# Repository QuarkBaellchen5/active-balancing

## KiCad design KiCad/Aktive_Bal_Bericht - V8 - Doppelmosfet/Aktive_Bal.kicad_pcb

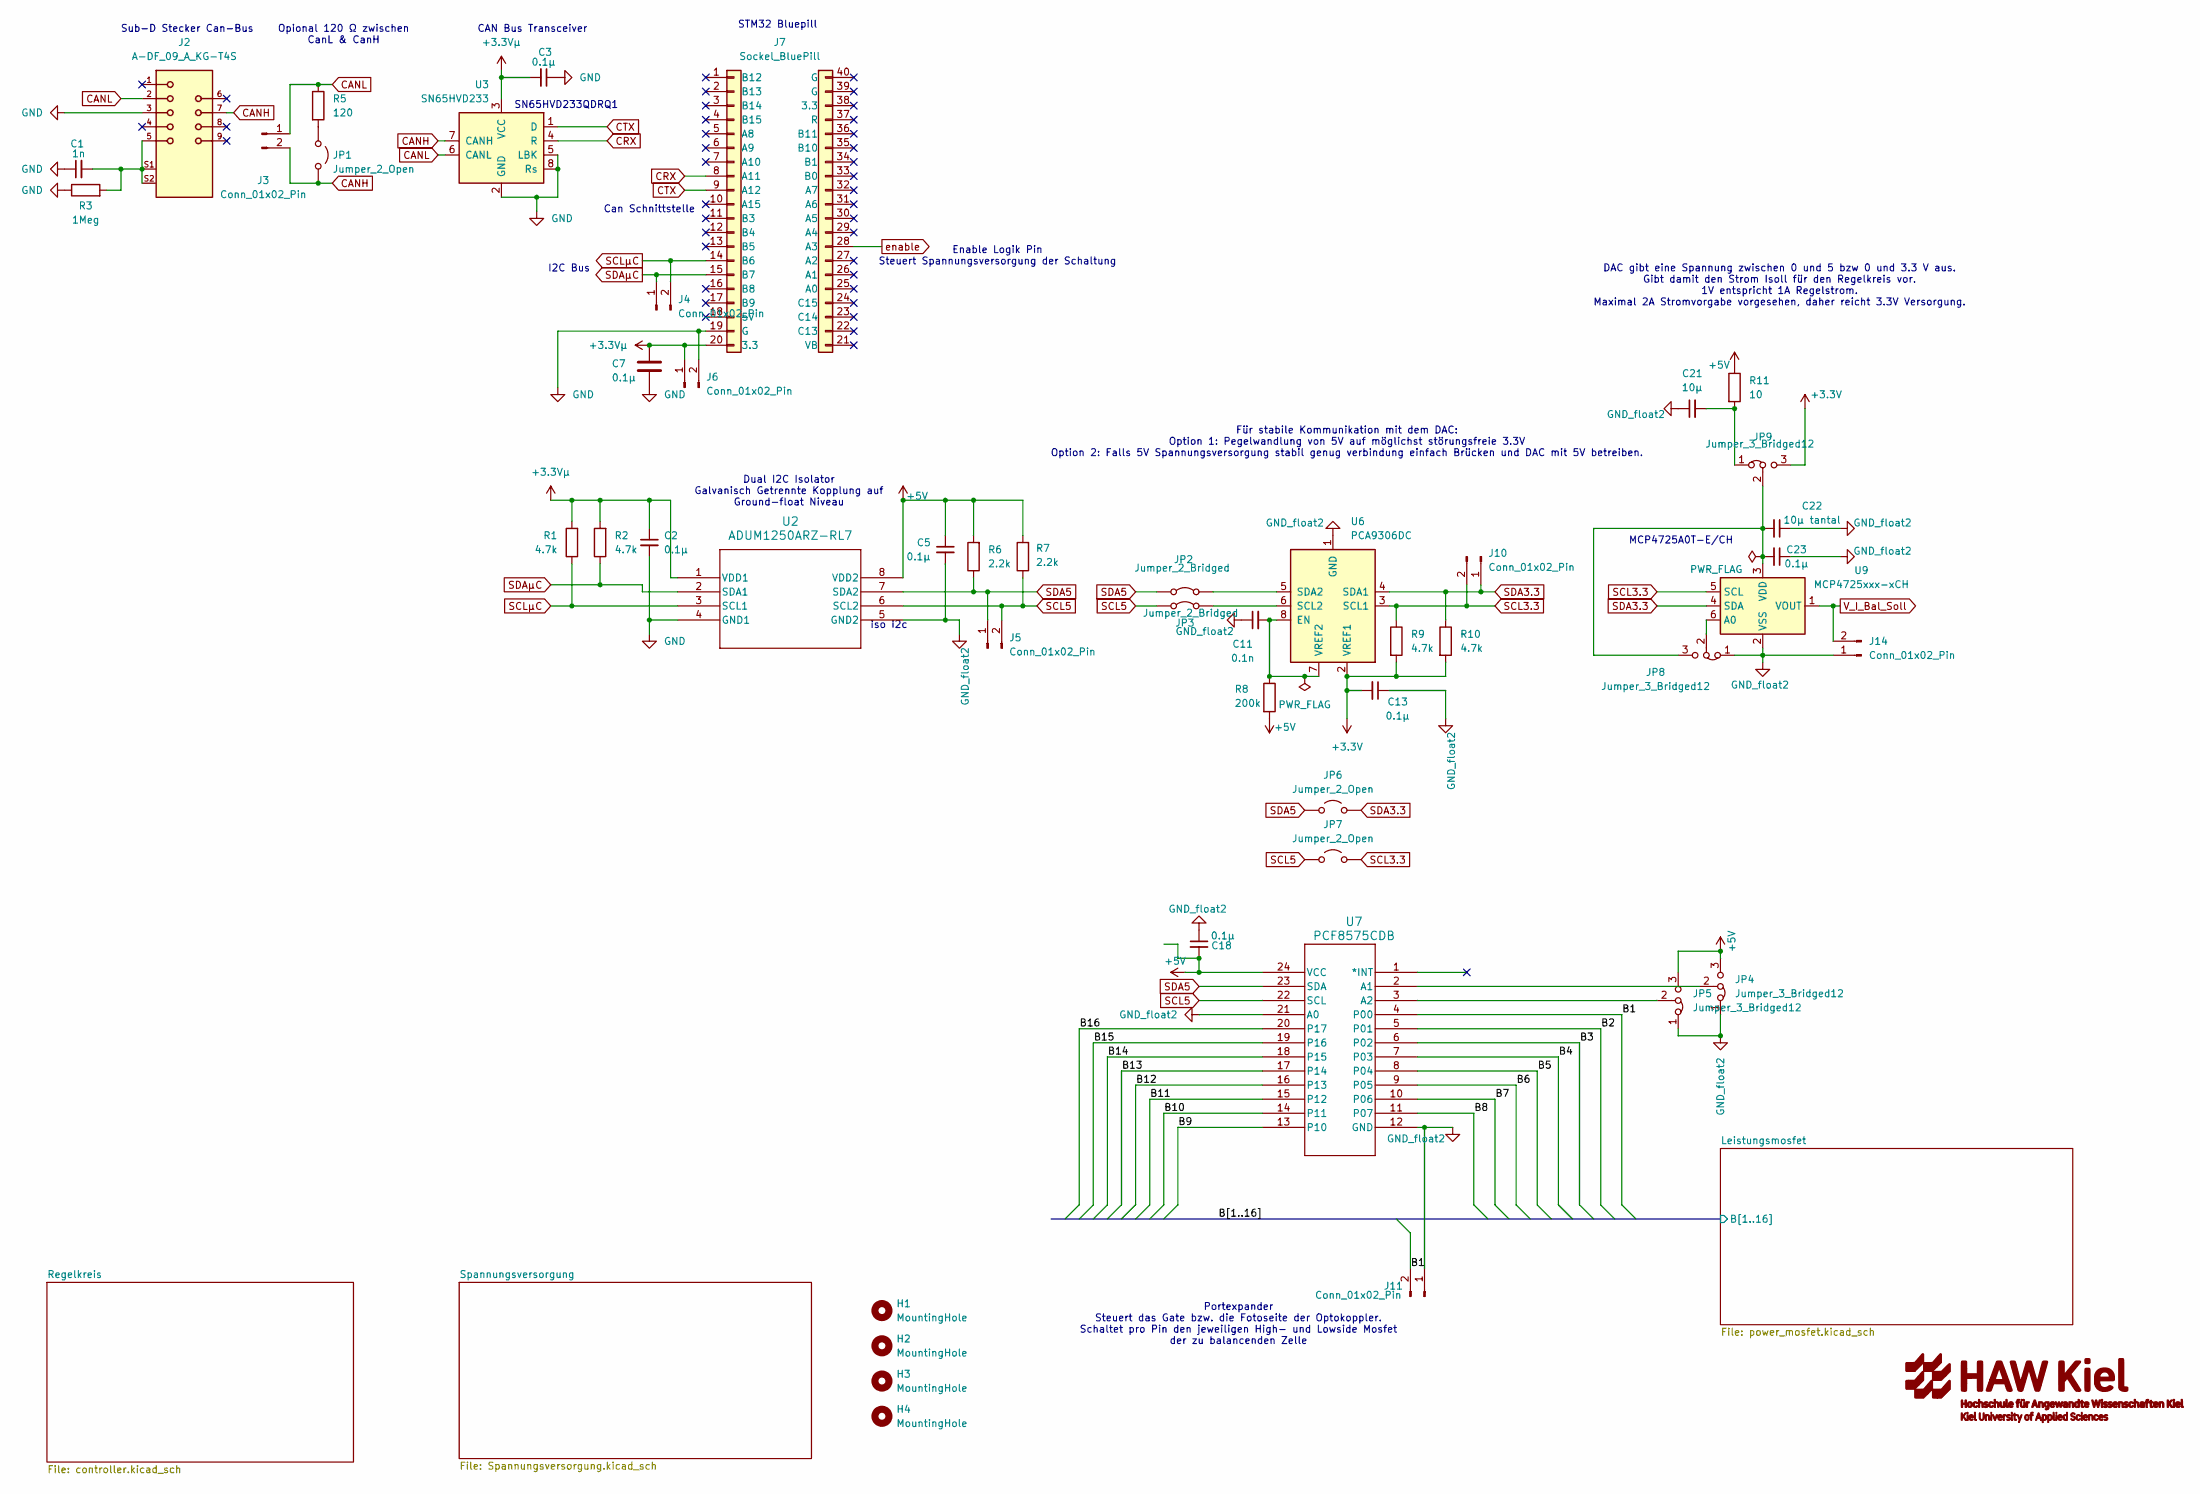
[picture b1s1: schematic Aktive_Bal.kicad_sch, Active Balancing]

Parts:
C1: 1n; C_0805_2012Metric
C2, C3, C5, C7, C13, C18, C23: 0.1µ; C_0805_2012Metric
C11: 0.1n; C_0805_2012Metric
C21: 10µ; C_0805_2012Metric
C22: 10µ tantal; C_0805_2012Metric
H1, H2, H3, H4: MountingHole; MountingHole_3.2mm_M3
J2: A-DF_09_A_KG-T4S; ASSMANN_A-DF_09_A_KG-T4S; PARTREV 05
J3, J4, J5, J6, J10, J11, J14: Conn_01x02_Pin; PinHeader_1x02_P2.54mm_Vertical
J7: Sockel_BluePill; SockelBluepill Dupont leisten
JP1, JP6, JP7: Jumper_2_Open; PinHeader_1x02_P2.54mm_Vertical
JP2, JP3: Jumper_2_Bridged; PinHeader_1x02_P2.54mm_Vertical
JP4, JP5, JP8, JP9: Jumper_3_Bridged12; PinHeader_1x03_P2.54mm_Vertical
R1, R2, R9, R10: 4.7k; R_0805_2012Metric
R3: 1Meg; R_0805_2012Metric
R5: 120; R_0805_2012Metric
R6, R7: 2.2k; R_0805_2012Metric
R8: 200k; R_0805_2012Metric
R11: 10; R_0805_2012Metric
U2: ADUM1250ARZ-RL7; ADUM1250ARZ-RL7_R_8_ADI-M
U3: SN65HVD233; SOIC-8_3.9x4.9mm_P1.27mm
U6: PCA9306DC; VSSOP-8_2.3x2mm_P0.5mm
U7: PCF8575CDB; PCF8575CDB_SSOP-24_5.3x8.2mm_P0.65mm
U9: MCP4725xxx-xCH; SOT-23-6

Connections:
+3.3V: C13.2, JP9.3 (B), R9.2, R10.2, U6.2 (VREF1); also elsewhere on the board
+3.3Vµ: C2.1, C3.2, C7.1, J6.1, J7.20 (3.3), R1.2, R2.2, U2.1 (VDD1), U3.3 (VCC)
+5V: C5.1, C18.2, JP4.3 (B), JP5.3 (B), R6.2, R7.2, R8.2, R11.1, U2.8 (VDD2), U7.24 (VCC); also elsewhere on the board
/B1: J11.2, U7.4 (P00); also elsewhere on the board
/B2: U7.5 (P01); also elsewhere on the board
/B3: U7.6 (P02); also elsewhere on the board
/B4: U7.7 (P03); also elsewhere on the board
/B5: U7.8 (P04); also elsewhere on the board
/B6: U7.9 (P05); also elsewhere on the board
/B7: U7.10 (P06); also elsewhere on the board
/B8: U7.11 (P07); also elsewhere on the board
/B9: U7.13 (P10); also elsewhere on the board
/B10: U7.14 (P11); also elsewhere on the board
/B11: U7.15 (P12); also elsewhere on the board
/B12: U7.16 (P13); also elsewhere on the board
/B13: U7.17 (P14); also elsewhere on the board
/B14: U7.18 (P15); also elsewhere on the board
/B15: U7.19 (P16); also elsewhere on the board
/B16: U7.20 (P17); also elsewhere on the board
CANH: J2.7, J3.2, JP1.2 (B), U3.7 (CANH)
CANL: J2.2 (TXD), J3.1, R5.1, U3.6 (CANL)
CRX: J7.8 (A11), U3.4 (R)
CTX: J7.9 (A12), U3.1 (D)
GND: C1.1, C2.2, C3.1, C7.2, J2.3 (RXD), J6.2, J7.19 (G), R3.1, U2.4 (GND1), U3.2 (GND), U3.5 (LBK), U3.8 (Rs); also elsewhere on the board
GND_float2: C5.2, C11.1, C13.1, C18.1, C21.1, C22.1, C23.1, J11.1, J14.1, JP4.1 (A), JP5.1 (A), JP8.1 (A), U2.5 (GND2), U6.1 (GND), U7.12 (GND), U7.21 (A0), U9.2 (VSS); also elsewhere on the board
unnamed: C1.2, J2.5 (GND), J2.S1 (SHIELD), J2.S2 (SHIELD__1), R3.2
unnamed: JP1.1 (A), R5.2
unnamed: JP2.2 (B), U6.5 (SDA2)
unnamed: JP3.2 (B), U6.6 (SCL2)
unnamed: JP4.2 (C), U7.2 (A1)
unnamed: JP5.2 (C), U7.3 (A2)
unnamed: C22.2, C23.2, JP8.3 (B), JP9.2 (C), U9.3 (VDD)
unnamed: JP8.2 (C), U9.6 (A0)
unnamed: C21.2, JP9.1 (A), R11.2
unnamed: C11.2, R8.1, U6.7 (VREF2), U6.8 (EN)
SCL3.3: J10.2, JP7.2 (B), R9.1, U6.3 (SCL1), U9.5 (SCL)
SCL5: J5.2, JP3.1 (A), JP7.1 (A), R7.1, U2.6 (SCL2), U7.22 (SCL)
SCLµC: J4.2, J7.14 (B6), R1.1, U2.3 (SCL1)
SDA3.3: J10.1, JP6.2 (B), R10.1, U6.4 (SDA1), U9.4 (SDA)
SDA5: J5.1, JP2.1 (A), JP6.1 (A), R6.1, U2.7 (SDA2), U7.23 (SDA)
SDAµC: J4.1, J7.15 (B7), R2.1, U2.2 (SDA1)
V_I_Bal_Soll: J14.2, U9.1 (VOUT); also elsewhere on the board
enable: J7.28 (A3); also elsewhere on the board

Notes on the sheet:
SN65HVD233QDRQ1
MCP4725A0T-E/CH
Enable Logik Pin Steuert Spannungsversorgung der Schaltung
CAN Bus Transceiver
Sub-D Stecker Can-Bus
Opional 120 Ω zwischen CanL & CanH
DAC gibt eine Spannung zwischen 0 und 5 bzw 0 und 3.3 V aus. Gibt damit den Strom Isoll für den Regelkreis vor. 1V entspricht 1A Regelstrom. Maximal 2A Stromvorgabe vorgesehen, daher reicht 3.3V Versorgung.
Für stabile Kommunikation mit dem DAC: Option 1: Pegelwandlung von 5V auf möglichst störungsfreie 3.3V Option 2: Falls 5V Spannungsversorgung stabil genug verbindung einfach Brücken und DAC mit 5V betreiben.
Dual I2C Isolator Galvanisch Getrennte Kopplung auf Ground-float Niveau
Portexpander Steuert das Gate bzw. die Fotoseite der Optokoppler. Schaltet pro Pin den jeweiligen High- und Lowside Mosfet der zu balancenden Zelle
I2C Bus
STM32 Bluepill
iso i2c
Can Schnittstelle

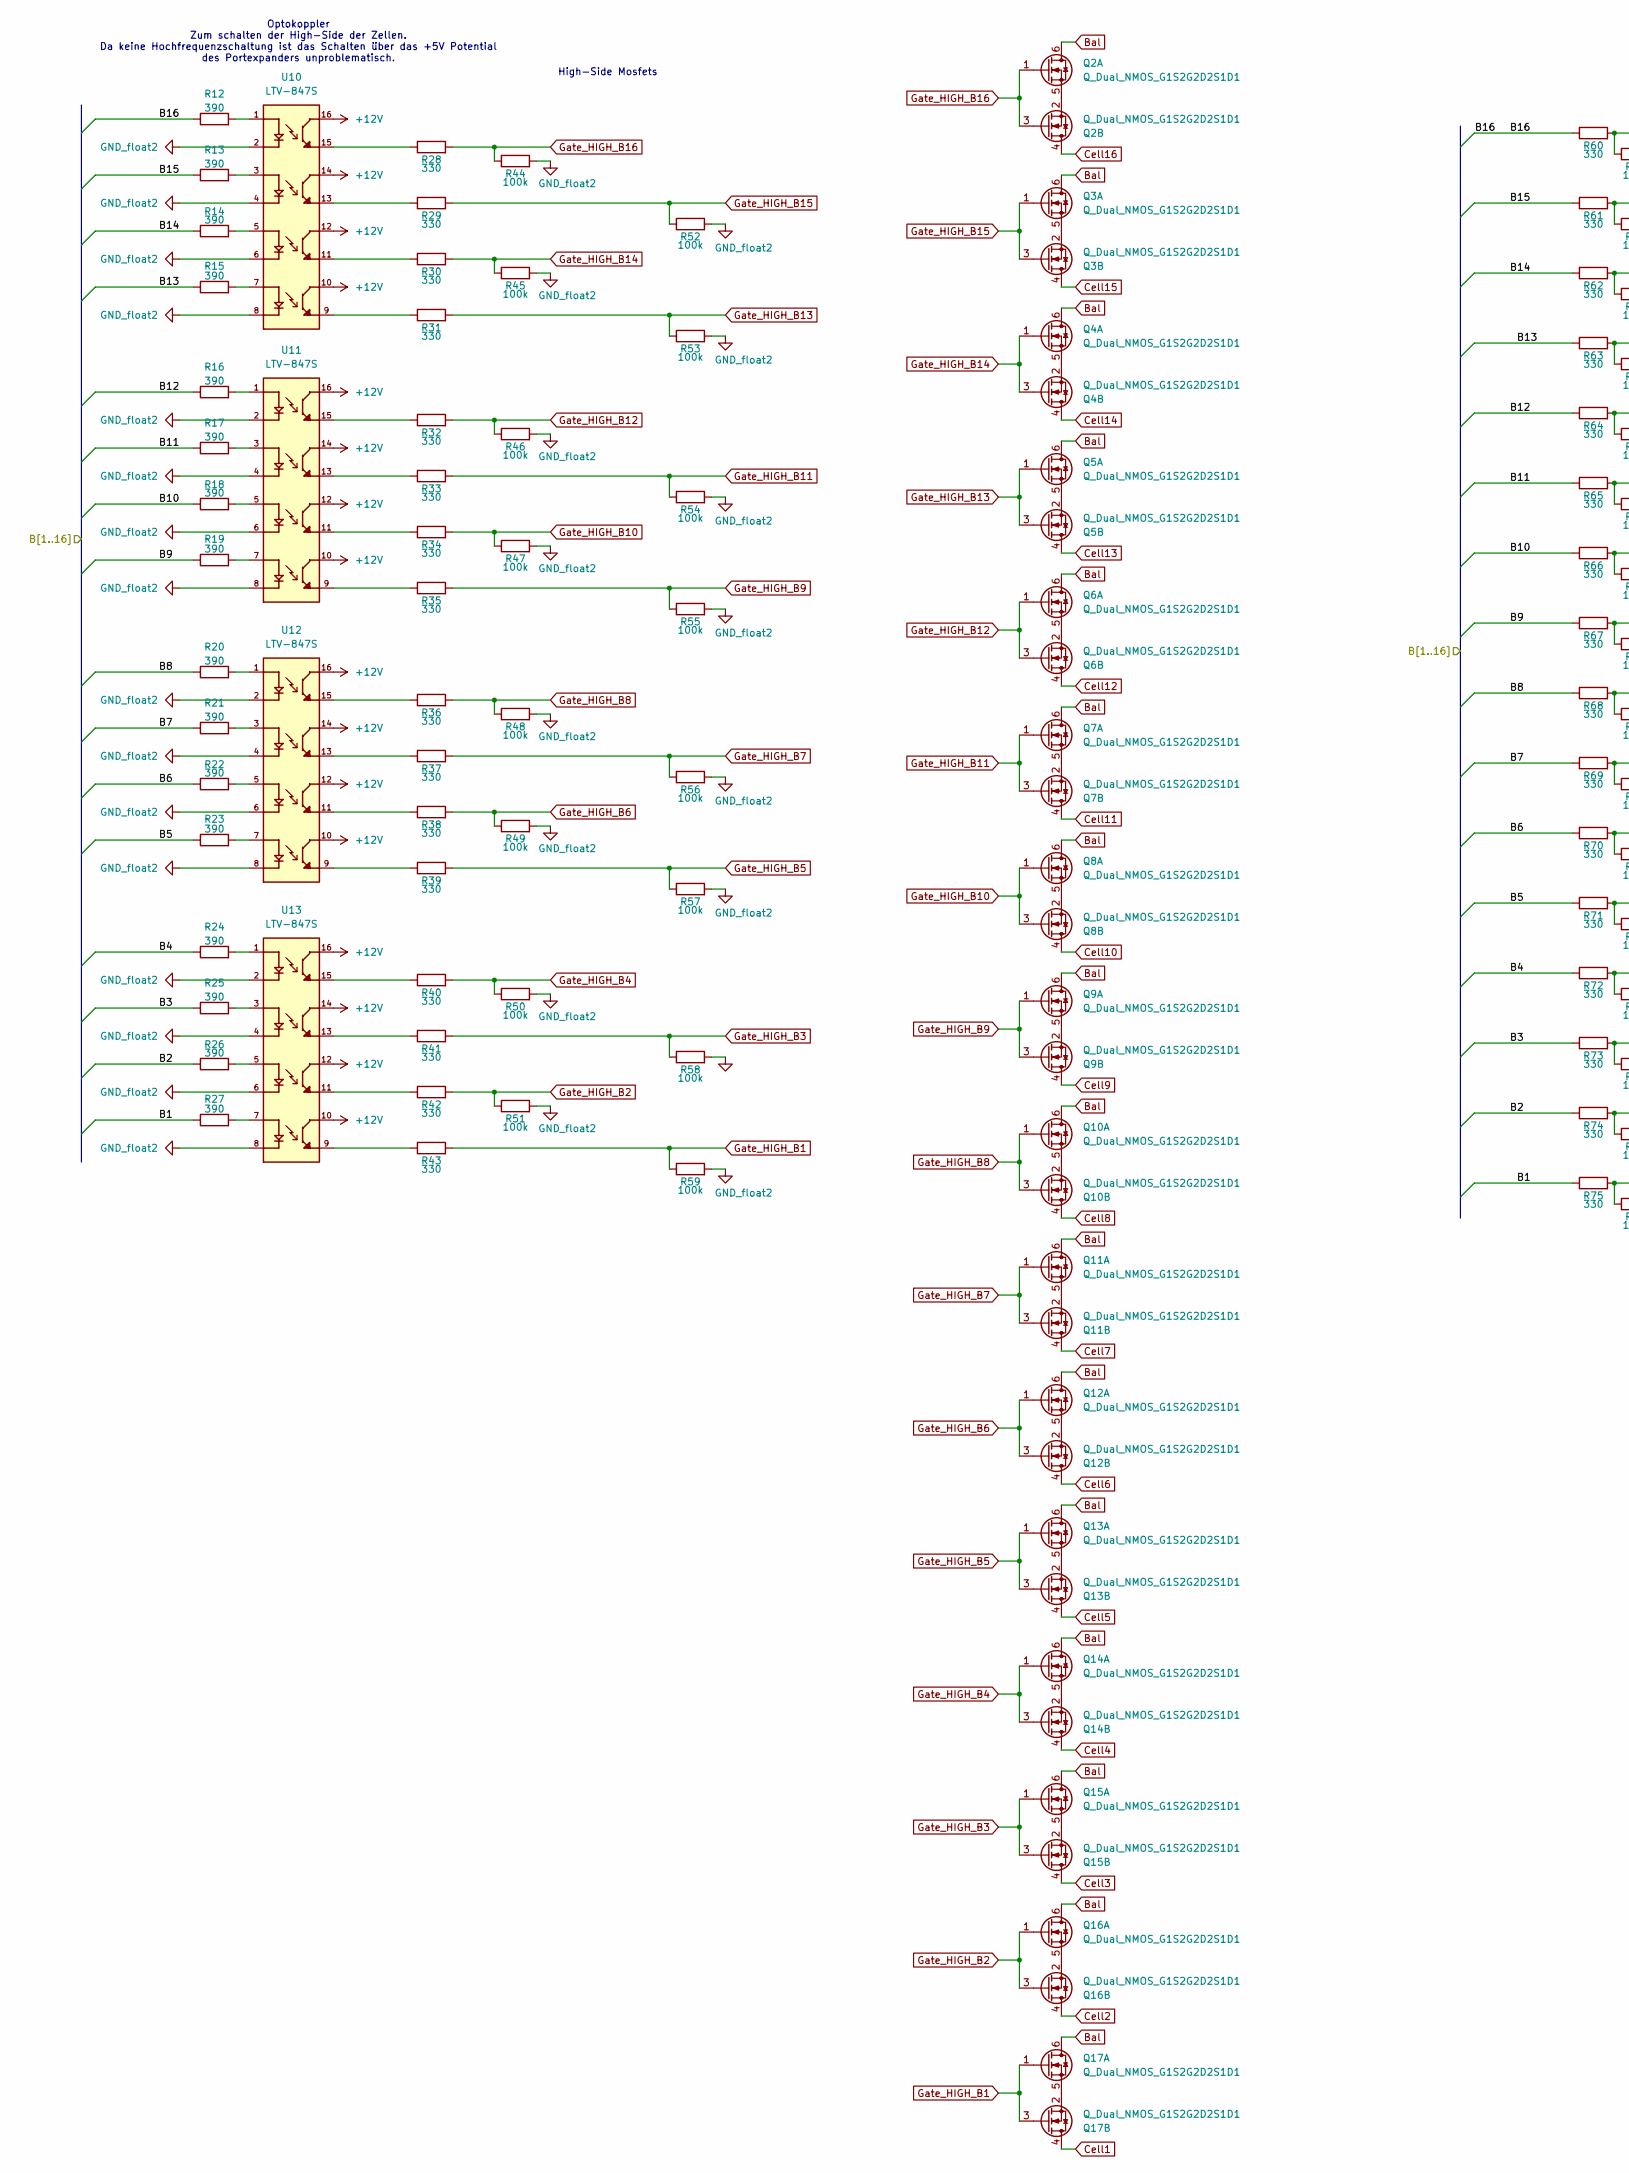
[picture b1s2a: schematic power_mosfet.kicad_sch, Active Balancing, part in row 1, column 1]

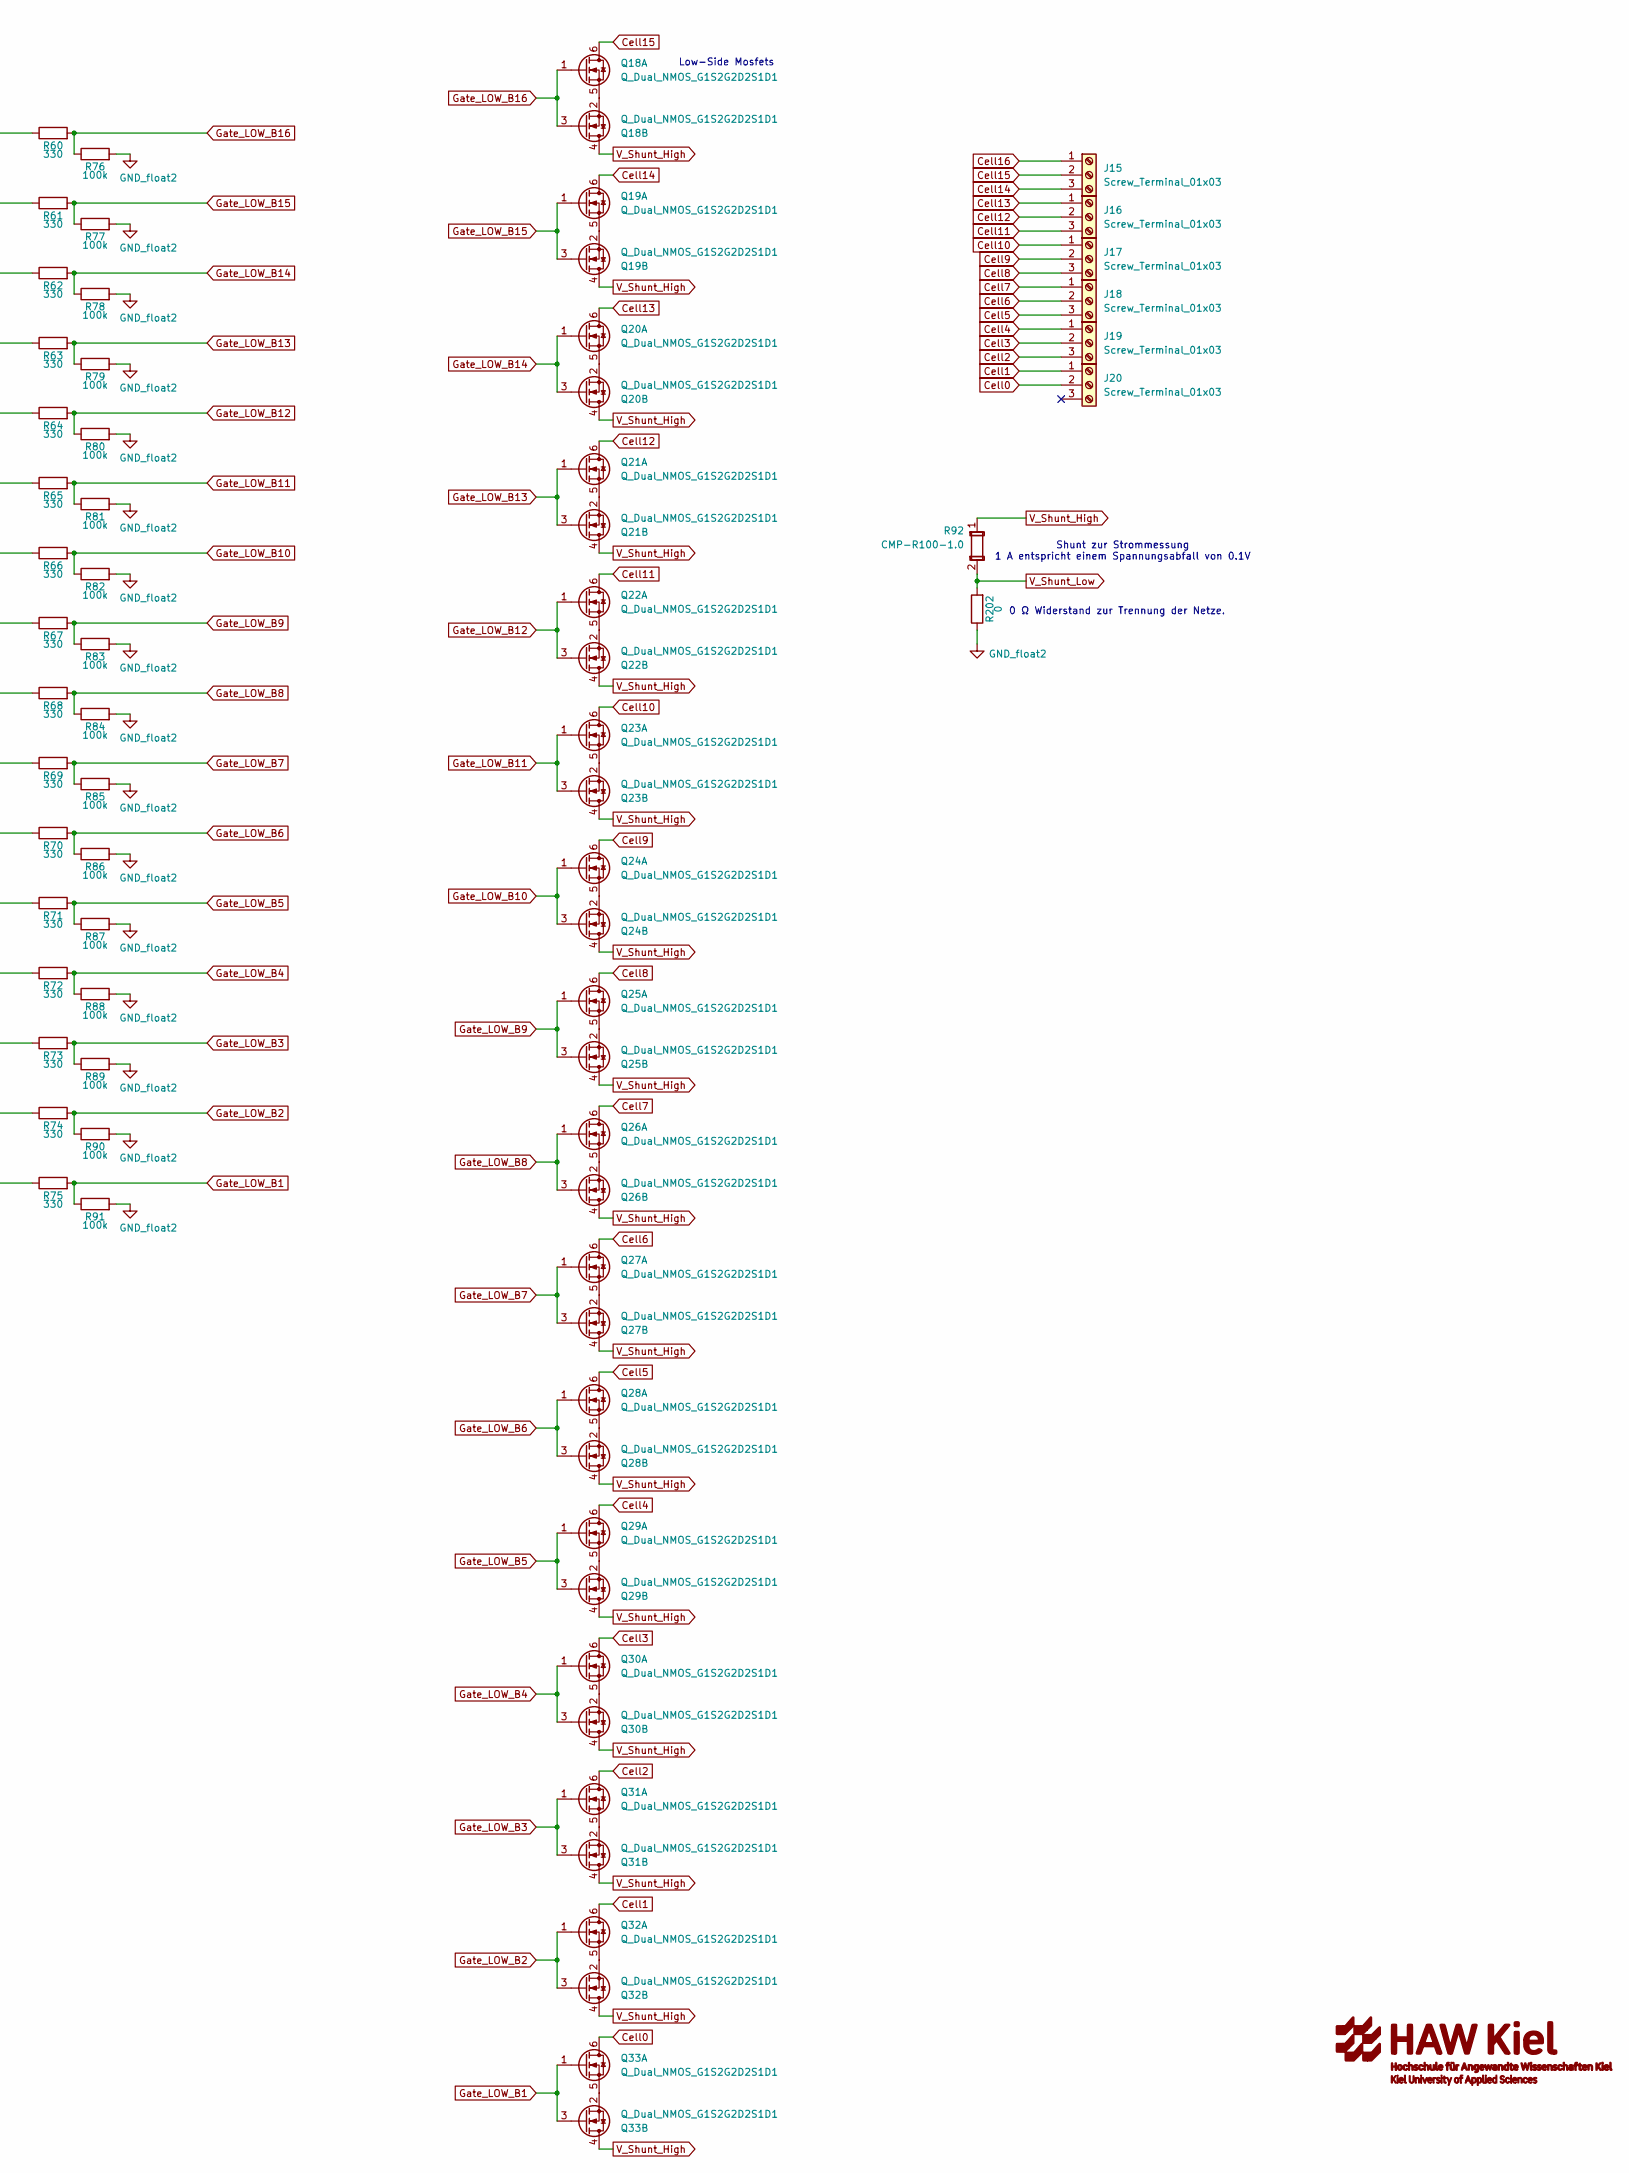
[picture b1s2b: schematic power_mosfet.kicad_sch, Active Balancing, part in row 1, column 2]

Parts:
J15, J16, J17, J18, J19, J20: Screw_Terminal_01x03; TerminalBlock_4Ucon_1x03_P3.50mm_Horizontal_3d
Q2, Q3, Q4, Q5, Q6, Q7, Q8, Q9, Q10, Q11, Q12, Q13, Q14, Q15, Q16, Q17, Q18, Q19, Q20, Q21, Q22, Q23, Q24, Q25, Q26, Q27, Q28, Q29, Q30, Q31, Q32, Q33: Q_Dual_NMOS_G1S2G2D2S1D1; SOT-23-6
R12, R13, R14, R15, R16, R17, R18, R19, R20, R21, R22, R23, R24, R25, R26, R27: 390; R_0805_2012Metric
R28, R29, R30, R31, R32, R33, R34, R35, R36, R37, R38, R39, R40, R41, R42, R43, R60, R61, R62, R63, R64, R65, R66, R67, R68, R69, R70, R71, R72, R73, R74, R75: 330; R_0805_2012Metric
R44, R45, R46, R47, R48, R49, R50, R51, R52, R53, R54, R55, R56, R57, R58, R59, R76, R77, R78, R79, R80, R81, R82, R83, R84, R85, R86, R87, R88, R89, R90, R91: 100k; R_0805_2012Metric
R92: CMP-R100-1.0
R202: 0; R_0805_2012Metric
U10, U11, U12, U13: LTV-847S; SOIC254P1016X460-16N; PARTREV January 2010

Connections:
+12V: U10.10, U10.12, U10.14, U10.16, U11.10, U11.12, U11.14, U11.16, U12.10, U12.12, U12.14, U12.16, U13.10, U13.12, U13.14, U13.16; also elsewhere on the board
/B1: R27.1, R75.1; also elsewhere on the board
/B2: R26.1, R74.1; also elsewhere on the board
/B3: R25.1, R73.1; also elsewhere on the board
/B4: R24.1, R72.1; also elsewhere on the board
/B5: R23.1, R71.1; also elsewhere on the board
/B6: R22.1, R70.1; also elsewhere on the board
/B7: R21.1, R69.1; also elsewhere on the board
/B8: R20.1, R68.1; also elsewhere on the board
/B9: R19.1, R67.1; also elsewhere on the board
/B10: R18.1, R66.1; also elsewhere on the board
/B11: R17.1, R65.1; also elsewhere on the board
/B12: R16.1, R64.1; also elsewhere on the board
/B13: R15.1, R63.1; also elsewhere on the board
/B14: R14.1, R62.1; also elsewhere on the board
/B15: R13.1, R61.1; also elsewhere on the board
/B16: R12.1, R60.1; also elsewhere on the board
Bal: Q2.6 (D), Q3.6 (D), Q4.6 (D), Q5.6 (D), Q6.6 (D), Q7.6 (D), Q8.6 (D), Q9.6 (D), Q10.6 (D), Q11.6 (D), Q12.6 (D), Q13.6 (D), Q14.6 (D), Q15.6 (D), Q16.6 (D), Q17.6 (D); also elsewhere on the board
Cell0: J20.2, Q33.6 (D)
Cell1: J20.1, Q17.4 (D), Q32.6 (D)
Cell2: J19.3, Q16.4 (D), Q31.6 (D)
Cell3: J19.2, Q15.4 (D), Q30.6 (D)
Cell4: J19.1, Q14.4 (D), Q29.6 (D)
Cell5: J18.3, Q13.4 (D), Q28.6 (D)
Cell6: J18.2, Q12.4 (D), Q27.6 (D)
Cell7: J18.1, Q11.4 (D), Q26.6 (D)
Cell8: J17.3, Q10.4 (D), Q25.6 (D)
Cell9: J17.2, Q9.4 (D), Q24.6 (D)
Cell10: J17.1, Q8.4 (D), Q23.6 (D)
Cell11: J16.3, Q7.4 (D), Q22.6 (D)
Cell12: J16.2, Q6.4 (D), Q21.6 (D)
Cell13: J16.1, Q5.4 (D), Q20.6 (D)
Cell14: J15.3, Q4.4 (D), Q19.6 (D)
Cell15: J15.2, Q3.4 (D), Q18.6 (D)
Cell16: J15.1, Q2.4 (D)
GND_float2: R44.2, R45.2, R46.2, R47.2, R48.2, R49.2, R50.2, R51.2, R52.2, R53.2, R54.2, R55.2, R56.2, R57.2, R58.2, R59.2, R76.2, R77.2, R78.2, R79.2, R80.2, R81.2, R82.2, R83.2, R84.2, R85.2, R86.2, R87.2, R88.2, R89.2, R90.2, R91.2, R202.1, U10.2, U10.4, U10.6, U10.8, U11.2, U11.4, U11.6, U11.8, U12.2, U12.4, U12.6, U12.8, U13.2, U13.4, U13.6, U13.8; also elsewhere on the board
Gate_HIGH_B1: Q17.1 (G), Q17.3 (G), R43.2, R59.1
Gate_HIGH_B2: Q16.1 (G), Q16.3 (G), R42.2, R51.1
Gate_HIGH_B3: Q15.1 (G), Q15.3 (G), R41.2, R58.1
Gate_HIGH_B4: Q14.1 (G), Q14.3 (G), R40.2, R50.1
Gate_HIGH_B5: Q13.1 (G), Q13.3 (G), R39.2, R57.1
Gate_HIGH_B6: Q12.1 (G), Q12.3 (G), R38.2, R49.1
Gate_HIGH_B7: Q11.1 (G), Q11.3 (G), R37.2, R56.1
Gate_HIGH_B8: Q10.1 (G), Q10.3 (G), R36.2, R48.1
Gate_HIGH_B9: Q9.1 (G), Q9.3 (G), R35.2, R55.1
Gate_HIGH_B10: Q8.1 (G), Q8.3 (G), R34.2, R47.1
Gate_HIGH_B11: Q7.1 (G), Q7.3 (G), R33.2, R54.1
Gate_HIGH_B12: Q6.1 (G), Q6.3 (G), R32.2, R46.1
Gate_HIGH_B13: Q5.1 (G), Q5.3 (G), R31.2, R53.1
Gate_HIGH_B14: Q4.1 (G), Q4.3 (G), R30.2, R45.1
Gate_HIGH_B15: Q3.1 (G), Q3.3 (G), R29.2, R52.1
Gate_HIGH_B16: Q2.1 (G), Q2.3 (G), R28.2, R44.1
Gate_LOW_B1: Q33.1 (G), Q33.3 (G), R75.2, R91.1
Gate_LOW_B2: Q32.1 (G), Q32.3 (G), R74.2, R90.1
Gate_LOW_B3: Q31.1 (G), Q31.3 (G), R73.2, R89.1
Gate_LOW_B4: Q30.1 (G), Q30.3 (G), R72.2, R88.1
Gate_LOW_B5: Q29.1 (G), Q29.3 (G), R71.2, R87.1
Gate_LOW_B6: Q28.1 (G), Q28.3 (G), R70.2, R86.1
Gate_LOW_B7: Q27.1 (G), Q27.3 (G), R69.2, R85.1
Gate_LOW_B8: Q26.1 (G), Q26.3 (G), R68.2, R84.1
Gate_LOW_B9: Q25.1 (G), Q25.3 (G), R67.2, R83.1
Gate_LOW_B10: Q24.1 (G), Q24.3 (G), R66.2, R82.1
Gate_LOW_B11: Q23.1 (G), Q23.3 (G), R65.2, R81.1
Gate_LOW_B12: Q22.1 (G), Q22.3 (G), R64.2, R80.1
Gate_LOW_B13: Q21.1 (G), Q21.3 (G), R63.2, R79.1
Gate_LOW_B14: Q20.1 (G), Q20.3 (G), R62.2, R78.1
Gate_LOW_B15: Q19.1 (G), Q19.3 (G), R61.2, R77.1
Gate_LOW_B16: Q18.1 (G), Q18.3 (G), R60.2, R76.1
unnamed: Q2.2 (S), Q2.5 (S)
unnamed: Q3.2 (S), Q3.5 (S)
unnamed: Q4.2 (S), Q4.5 (S)
unnamed: Q5.2 (S), Q5.5 (S)
unnamed: Q6.2 (S), Q6.5 (S)
unnamed: Q7.2 (S), Q7.5 (S)
unnamed: Q8.2 (S), Q8.5 (S)
unnamed: Q9.2 (S), Q9.5 (S)
unnamed: Q10.2 (S), Q10.5 (S)
unnamed: Q11.2 (S), Q11.5 (S)
unnamed: Q12.2 (S), Q12.5 (S)
unnamed: Q13.2 (S), Q13.5 (S)
unnamed: Q14.2 (S), Q14.5 (S)
unnamed: Q15.2 (S), Q15.5 (S)
unnamed: Q16.2 (S), Q16.5 (S)
unnamed: Q17.2 (S), Q17.5 (S)
unnamed: Q18.2 (S), Q18.5 (S)
unnamed: Q19.2 (S), Q19.5 (S)
unnamed: Q20.2 (S), Q20.5 (S)
unnamed: Q21.2 (S), Q21.5 (S)
unnamed: Q22.2 (S), Q22.5 (S)
unnamed: Q23.2 (S), Q23.5 (S)
unnamed: Q24.2 (S), Q24.5 (S)
unnamed: Q25.2 (S), Q25.5 (S)
unnamed: Q26.2 (S), Q26.5 (S)
unnamed: Q27.2 (S), Q27.5 (S)
unnamed: Q28.2 (S), Q28.5 (S)
unnamed: Q29.2 (S), Q29.5 (S)
unnamed: Q30.2 (S), Q30.5 (S)
unnamed: Q31.2 (S), Q31.5 (S)
unnamed: Q32.2 (S), Q32.5 (S)
unnamed: Q33.2 (S), Q33.5 (S)
unnamed: R12.2, U10.1
unnamed: R13.2, U10.3
unnamed: R14.2, U10.5
unnamed: R15.2, U10.7
unnamed: R16.2, U11.1
unnamed: R17.2, U11.3
unnamed: R18.2, U11.5
unnamed: R19.2, U11.7
unnamed: R20.2, U12.1
unnamed: R21.2, U12.3
unnamed: R22.2, U12.5
unnamed: R23.2, U12.7
unnamed: R24.2, U13.1
unnamed: R25.2, U13.3
unnamed: R26.2, U13.5
unnamed: R27.2, U13.7
unnamed: R28.1, U10.15
unnamed: R29.1, U10.13
unnamed: R30.1, U10.11
unnamed: R31.1, U10.9
unnamed: R32.1, U11.15
unnamed: R33.1, U11.13
unnamed: R34.1, U11.11
unnamed: R35.1, U11.9
unnamed: R36.1, U12.15
unnamed: R37.1, U12.13
unnamed: R38.1, U12.11
unnamed: R39.1, U12.9
unnamed: R40.1, U13.15
unnamed: R41.1, U13.13
unnamed: R42.1, U13.11
unnamed: R43.1, U13.9
V_Shunt_High: Q18.4 (D), Q19.4 (D), Q20.4 (D), Q21.4 (D), Q22.4 (D), Q23.4 (D), Q24.4 (D), Q25.4 (D), Q26.4 (D), Q27.4 (D), Q28.4 (D), Q29.4 (D), Q30.4 (D), Q31.4 (D), Q32.4 (D), Q33.4 (D), R92.1; also elsewhere on the board
V_Shunt_Low: R92.2, R202.2; also elsewhere on the board

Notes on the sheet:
Optokoppler Zum schalten der High-Side der Zellen. Da keine Hochfrequenzschaltung ist das Schalten über das +5V Potential des Portexpanders unproblematisch.
Shunt zur Strommessung 1 A entspricht einem Spannungsabfall von 0.1V
High-Side Mosfets
0 Ω Widerstand zur Trennung der Netze.
Low-Side Mosfets

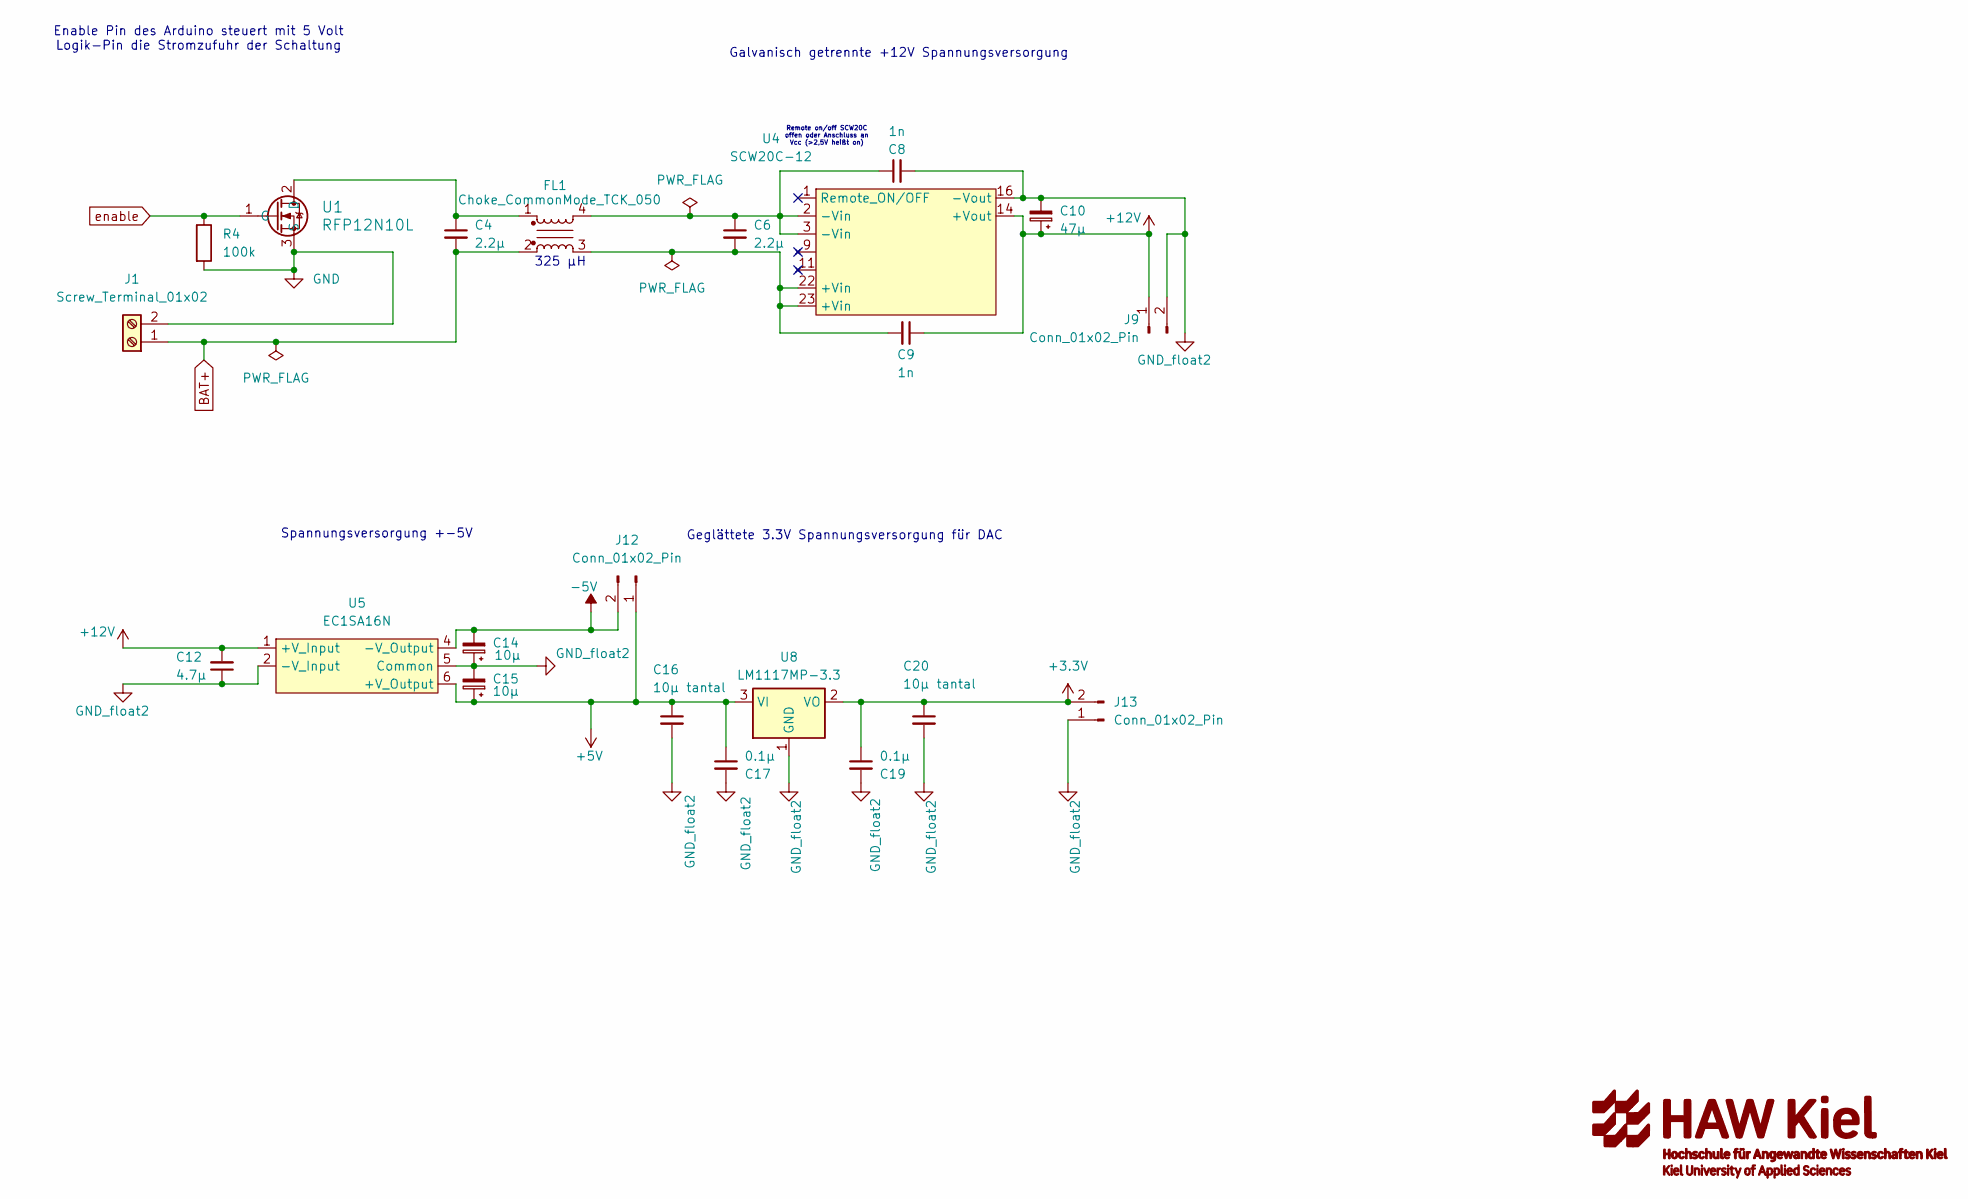
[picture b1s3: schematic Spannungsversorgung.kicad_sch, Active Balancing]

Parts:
C4, C6: 2.2µ; C_0805_2012Metric
C8, C9: 1n; C_0805_2012Metric
C10: 47µ; CP_Elec_5x5.3
C12: 4.7µ; C_0805_2012Metric
C14, C15: 10µ; CP_Elec_5x5.3
C16, C20: 10µ tantal; C_0805_2012Metric
C17, C19: 0.1µ; C_0805_2012Metric
FL1: Choke_CommonMode_TCK_050; common mode choke foot
J1: Screw_Terminal_01x02; 1-2-5mmTerminalBlock_MetzConnect_Type055_RT01502HDWU_1x02_P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
J9, J12, J13: Conn_01x02_Pin; PinHeader_1x02_P2.54mm_Vertical
R4: 100k; R_0805_2012Metric
U1: RFP12N10L; TO-220AB_ONS
U4: SCW20C-12
U5: EC1SA16N
U8: LM1117MP-3.3; SOT-223-3_TabPin2

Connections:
+3.3V: C19.1, C20.1, J13.2, U8.2 (VO); also elsewhere on the board
+5V: C15.1, C16.1, C17.1, J12.1, U5.6 (+V_Output), U8.3 (VI); also elsewhere on the board
+12V: C9.1, C10.1, C12.2, J9.1, U4.14 (+Vout), U5.1 (+V_Input); also elsewhere on the board
-5V: C14.2, J12.2, U5.4 (-V_Output); also elsewhere on the board
BAT+: C4.2, FL1.2, J1.1
GND: J1.2, R4.2, U1.3 (S); also elsewhere on the board
GND_float2: C8.2, C10.2, C12.1, C14.1, C15.2, C16.2, C17.2, C19.2, C20.2, J9.2, J13.1, U4.16 (-Vout), U5.2 (-V_Input), U5.5 (Common), U8.1 (GND); also elsewhere on the board
unnamed: C6.1, C8.1, FL1.4, U4.2 (-Vin), U4.3 (-Vin)
unnamed: C6.2, C9.2, FL1.3, U4.22 (+Vin), U4.23 (+Vin)
unnamed: C4.1, FL1.1, U1.2 (D)
enable: R4.1, U1.1 (G); also elsewhere on the board

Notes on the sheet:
Remote on/off SCW20C offen oder Anschluss an Vcc (>2,5V heißt on)
Enable Pin des Arduino steuert mit 5 Volt Logik-Pin die Stromzufuhr der Schaltung
Galvanisch getrennte +12V Spannungsversorgung
Geglättete 3.3V Spannungsversorgung für DAC
Spannungsversorgung +-5V
325 µH
